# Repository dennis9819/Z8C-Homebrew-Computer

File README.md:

# Z8C-Homebrew-Computer

# Using the build tools
The Z8C uses the zmac macro assembler (http://48k.ca/zmac.html)

To easily develop for my Z80 homebrew system, I designed a simple
assempler development environment. This packs the following tasks into one script:
* zmac assembly
* object file creation (for xmodem upload)
* monitor file creation (creates monitor commands for ascii upload)
* symbol table include file generation
* eeprom programming for the minipro

## Prequisites
* zmac - self-compiled version included in ./Utility.
* minipro (https://gitlab.com/DavidGriffith/minipro)
* binutils (apt-get install binutils-multiarch, 
    pacman -S aarch64-linux-gnu-binutils )

## Building a project
`./build.sh <dir> <asm filename>`
* `dir`: Path to the location of the asm file
* `asm filename`: name of the assembly file without suffix

```
    # e.g.:
    cd ./Utility
    ./build.sh ../OperatingSystem/monitor_v2  
    ./build.sh ../OperatingSystem/software  
```
## Building a project with a properties file

`./build.sh <dir>`
* `dir`: Path to the location of the asm file

The directory must contain a file called `properties.env`
This file can contain project-specific options.

Example:
```
export OPT_GEN_SYMBOLTABLE=1
export OPT_GEN_MONFILE=0
export OPT_GEN_OBJFILE=1
export OPT_WRITEROM=1
export FILENAME=main
```

### Options
* `OPT_GEN_SYMBOLTABLE` if set to 1: Generates the symbols.s file
* `OPT_GEN_MONFILE` if set to 1: Generates the monitor file
* `OPT_GEN_OBJFILE` if set to 1: Generates the object file
* `OPT_WRITEROM` if set to 1: Starts eeprom programmer
* `FILENAME` same as the `<asm filename>` paramter of the build script
* `ROOT_DIR` overrides the project root path. required if git is not used
* `EEPROM_PART` sets EEPROM part for minipro. Default: `AT28C256`

# System design
The Z80 Hombrew computer is modular computer system, designed arround a custom backplane.

## Available modules
### Z8C CPU/COM Board
* Z80 ZPU @ 4MHz (6MHz planned)
* 64 KiB SRAM
* 32 KiB EEPROM (R/W switchable)
* Z80 CTC with external 1.8432MHz Clock switchable per channel
* Z80 SIO (Up to 115200 BAUD possible @ X16 SIO prescaler)
* 1 FTDI Connector
* 1 RS232 DSUB-9 Port
* 8 front-facing DIP switches (currently used for baud-rate setup)
* Power-On-Reset Circuit

```
Memory Layout
       Default ($00 = 0x00)  Mode 1 ($00 = 0x02)  Mode 2 ($00 = 0x01)             
$0000 +--------------------+--------------------+--------------------+
      | EEPROM Lower 16KiB | EEPROM Upper 16KiB | SRAM               |
$4000 +--------------------+--------------------+                    |
      | SRAM               | SRAM               |                    | 
      |                    |                    |                    |
      |                    |                    |                    |
$FFFF +--------------------+--------------------+--------------------+

Note: In default mode and mode 1, the MEMAQ pin (pin a5 on backplane) 
      can be used to inject an external memory device in the $0000-$3FFF 
      window.

IO Addresses:
$00 Memory register
$01 DIP Switches
$04 CTC (First address)
$08 SIO (First address)
```

### Z8C MIO Board
* Z80 PIO (Used for GPIO and non Z80 compliant interrupt handling)
* VT82C42 PS/2 controller
* AM5911A (only usable with CPU-Clock under 3 MHz)
* PFC8584 I2C Controller
* DS1307 RTC
* 8-Bit GPIO Port

//TODO: Add more Info

### Z8C Disk Interface Board
* Intel 82C55 based IDE Interface
* FDC9266 Floppy Disk Controller

//TODO: Add more Info

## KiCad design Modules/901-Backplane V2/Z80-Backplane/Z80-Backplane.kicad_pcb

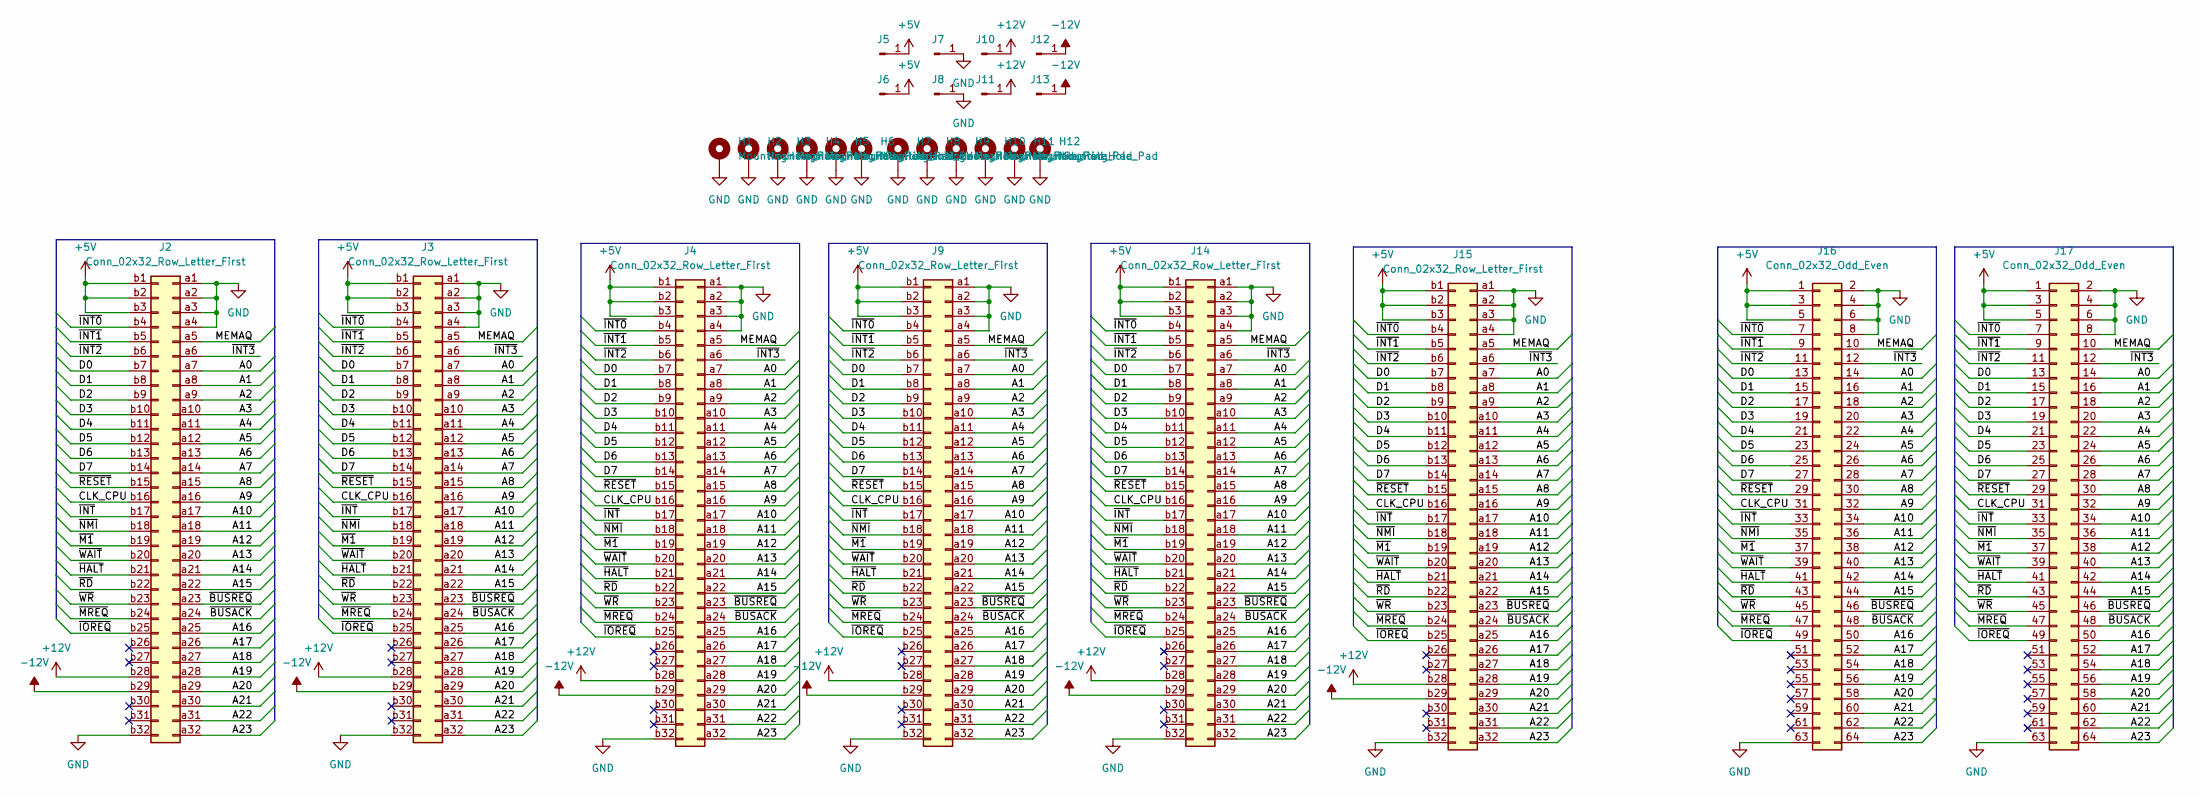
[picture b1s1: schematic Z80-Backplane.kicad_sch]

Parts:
H1, H2, H3, H4, H5, H6, H7, H8, H9, H10, H11, H12: MountingHole_Pad; MountingHole_2.7mm_M2.5_DIN965_Pad
J2, J3, J4, J9, J14, J15: Conn_02x32_Row_Letter_First; DIN41612_B_2x32_Female_Vertical_THT
J5, J6, J7, J8, J10, J11, J12, J13: Conn_01x01_Male; FS-P475
J16, J17: Conn_02x32_Odd_Even; IDC-Header_2x32_P2.54mm_Vertical

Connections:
+5V: J2.b1, J2.b2, J2.b3, J3.b1, J3.b2, J3.b3, J4.b1, J4.b2, J4.b3, J5.1, J6.1, J9.b1, J9.b2, J9.b3, J14.b1, J14.b2, J14.b3, J15.b1, J15.b2, J15.b3, J16.1, J16.3, J16.5, J17.1, J17.3, J17.5
+12V: J2.b28, J3.b28, J4.b28, J9.b28, J10.1, J11.1, J14.b28, J15.b28
-12V: J2.b29, J3.b29, J4.b29, J9.b29, J12.1, J13.1, J14.b29, J15.b29
/A0: J2.a7, J3.a7, J4.a7, J9.a7, J14.a7, J15.a7, J16.14, J17.14
/A1: J2.a8, J3.a8, J4.a8, J9.a8, J14.a8, J15.a8, J16.16, J17.16
/A2: J2.a9, J3.a9, J4.a9, J9.a9, J14.a9, J15.a9, J16.18, J17.18
/A3: J2.a10, J3.a10, J4.a10, J9.a10, J14.a10, J15.a10, J16.20, J17.20
/A4: J2.a11, J3.a11, J4.a11, J9.a11, J14.a11, J15.a11, J16.22, J17.22
/A5: J2.a12, J3.a12, J4.a12, J9.a12, J14.a12, J15.a12, J16.24, J17.24
/A6: J2.a13, J3.a13, J4.a13, J9.a13, J14.a13, J15.a13, J16.26, J17.26
/A7: J2.a14, J3.a14, J4.a14, J9.a14, J14.a14, J15.a14, J16.28, J17.28
/A8: J2.a15, J3.a15, J4.a15, J9.a15, J14.a15, J15.a15, J16.30, J17.30
/A9: J2.a16, J3.a16, J4.a16, J9.a16, J14.a16, J15.a16, J16.32, J17.32
/A10: J2.a17, J3.a17, J4.a17, J9.a17, J14.a17, J15.a17, J16.34, J17.34
/A11: J2.a18, J3.a18, J4.a18, J9.a18, J14.a18, J15.a18, J16.36, J17.36
/A12: J2.a19, J3.a19, J4.a19, J9.a19, J14.a19, J15.a19, J16.38, J17.38
/A13: J2.a20, J3.a20, J4.a20, J9.a20, J14.a20, J15.a20, J16.40, J17.40
/A14: J2.a21, J3.a21, J4.a21, J9.a21, J14.a21, J15.a21, J16.42, J17.42
/A15: J2.a22, J3.a22, J4.a22, J9.a22, J14.a22, J15.a22, J16.44, J17.44
/A16: J2.a25, J3.a25, J4.a25, J9.a25, J14.a25, J15.a25, J16.50, J17.50
/A17: J2.a26, J3.a26, J4.a26, J9.a26, J14.a26, J15.a26, J16.52, J17.52
/A18: J2.a27, J3.a27, J4.a27, J9.a27, J14.a27, J15.a27, J16.54, J17.54
/A19: J2.a28, J3.a28, J4.a28, J9.a28, J14.a28, J15.a28, J16.56, J17.56
/A20: J2.a29, J3.a29, J4.a29, J9.a29, J14.a29, J15.a29, J16.58, J17.58
/A21: J2.a30, J3.a30, J4.a30, J9.a30, J14.a30, J15.a30, J16.60, J17.60
/A22: J2.a31, J3.a31, J4.a31, J9.a31, J14.a31, J15.a31, J16.62, J17.62
/A23: J2.a32, J3.a32, J4.a32, J9.a32, J14.a32, J15.a32, J16.64, J17.64
/CLK_CPU: J2.b16, J3.b16, J4.b16, J9.b16, J14.b16, J15.b16, J16.31, J17.31
/D0: J2.b7, J3.b7, J4.b7, J9.b7, J14.b7, J15.b7, J16.13, J17.13
/D1: J2.b8, J3.b8, J4.b8, J9.b8, J14.b8, J15.b8, J16.15, J17.15
/D2: J2.b9, J3.b9, J4.b9, J9.b9, J14.b9, J15.b9, J16.17, J17.17
/D3: J2.b10, J3.b10, J4.b10, J9.b10, J14.b10, J15.b10, J16.19, J17.19
/D4: J2.b11, J3.b11, J4.b11, J9.b11, J14.b11, J15.b11, J16.21, J17.21
/D5: J2.b12, J3.b12, J4.b12, J9.b12, J14.b12, J15.b12, J16.23, J17.23
/D6: J2.b13, J3.b13, J4.b13, J9.b13, J14.b13, J15.b13, J16.25, J17.25
/D7: J2.b14, J3.b14, J4.b14, J9.b14, J14.b14, J15.b14, J16.27, J17.27
/MEMAQ: J2.a5, J3.a5, J4.a5, J9.a5, J14.a5, J15.a5, J16.10, J17.10
/~BUSACK: J2.a24, J3.a24, J4.a24, J9.a24, J14.a24, J15.a24, J16.48, J17.48
/~BUSREQ: J2.a23, J3.a23, J4.a23, J9.a23, J14.a23, J15.a23, J16.46, J17.46
/~HALT: J2.b21, J3.b21, J4.b21, J9.b21, J14.b21, J15.b21, J16.41, J17.41
/~INT0: J2.b4, J3.b4, J4.b4, J9.b4, J14.b4, J15.b4, J16.7, J17.7
/~INT1: J2.b5, J3.b5, J4.b5, J9.b5, J14.b5, J15.b5, J16.9, J17.9
/~INT2: J2.b6, J3.b6, J4.b6, J9.b6, J14.b6, J15.b6, J16.11, J17.11
/~INT3: J2.a6, J3.a6, J4.a6, J9.a6, J14.a6, J15.a6, J16.12, J17.12
/~INT: J2.b17, J3.b17, J4.b17, J9.b17, J14.b17, J15.b17, J16.33, J17.33
/~IOREQ: J2.b25, J3.b25, J4.b25, J9.b25, J14.b25, J15.b25, J16.49, J17.49
/~M1: J2.b19, J3.b19, J4.b19, J9.b19, J14.b19, J15.b19, J16.37, J17.37
/~MREQ: J2.b24, J3.b24, J4.b24, J9.b24, J14.b24, J15.b24, J16.47, J17.47
/~NMI: J2.b18, J3.b18, J4.b18, J9.b18, J14.b18, J15.b18, J16.35, J17.35
/~RD: J2.b22, J3.b22, J4.b22, J9.b22, J14.b22, J15.b22, J16.43, J17.43
/~RESET: J2.b15, J3.b15, J4.b15, J9.b15, J14.b15, J15.b15, J16.29, J17.29
/~WAIT: J2.b20, J3.b20, J4.b20, J9.b20, J14.b20, J15.b20, J16.39, J17.39
/~WR: J2.b23, J3.b23, J4.b23, J9.b23, J14.b23, J15.b23, J16.45, J17.45
GND: H1.1, H2.1, H3.1, H4.1, H5.1, H6.1, H7.1, H8.1, H9.1, H10.1, H11.1, H12.1, J2.a1, J2.a2, J2.a3, J2.a4, J2.b32, J3.a1, J3.a2, J3.a3, J3.a4, J3.b32, J4.a1, J4.a2, J4.a3, J4.a4, J4.b32, J7.1, J8.1, J9.a1, J9.a2, J9.a3, J9.a4, J9.b32, J14.a1, J14.a2, J14.a3, J14.a4, J14.b32, J15.a1, J15.a2, J15.a3, J15.a4, J15.b32, J16.2, J16.4, J16.6, J16.8, J16.63, J17.2, J17.4, J17.6, J17.8, J17.63

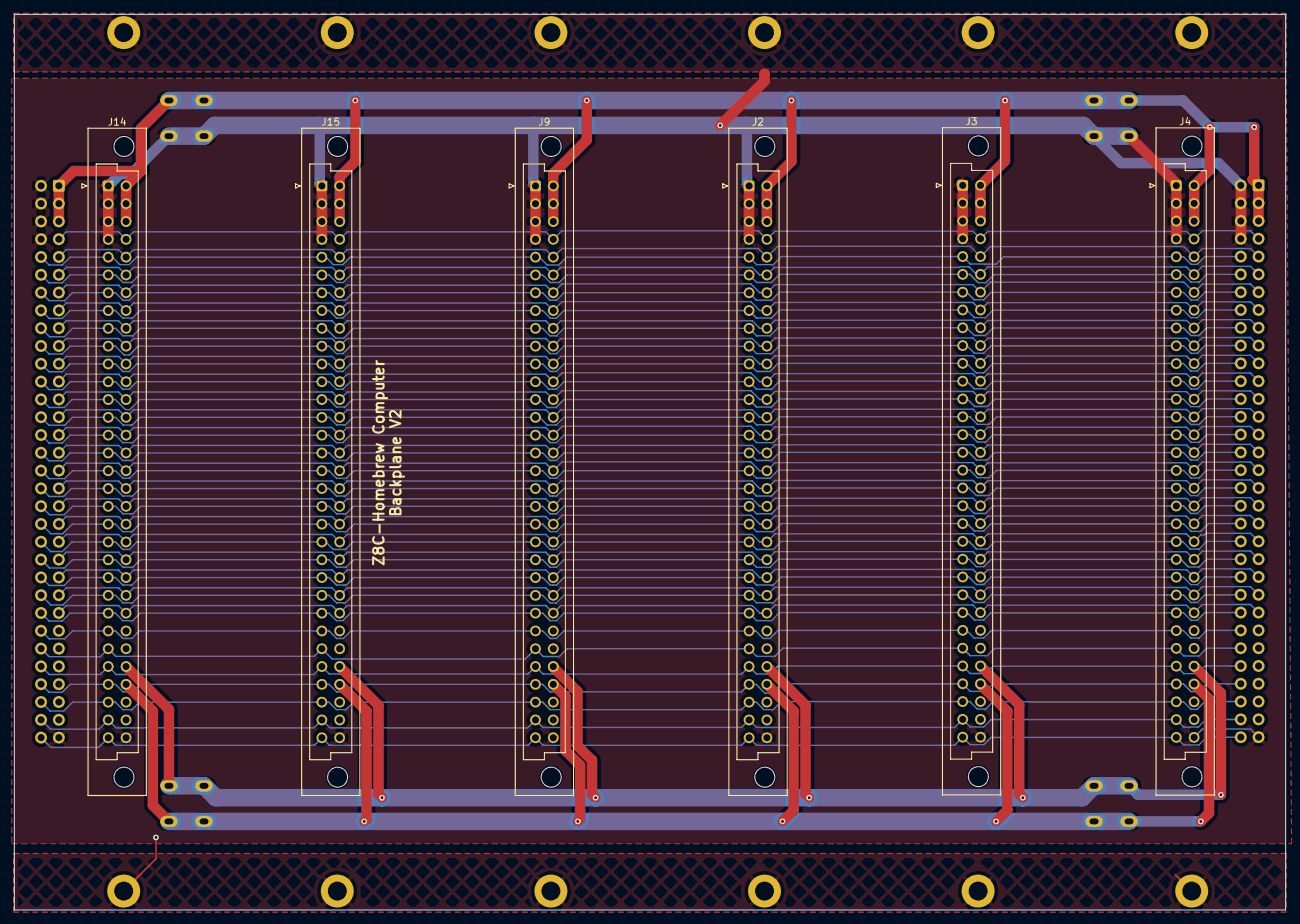
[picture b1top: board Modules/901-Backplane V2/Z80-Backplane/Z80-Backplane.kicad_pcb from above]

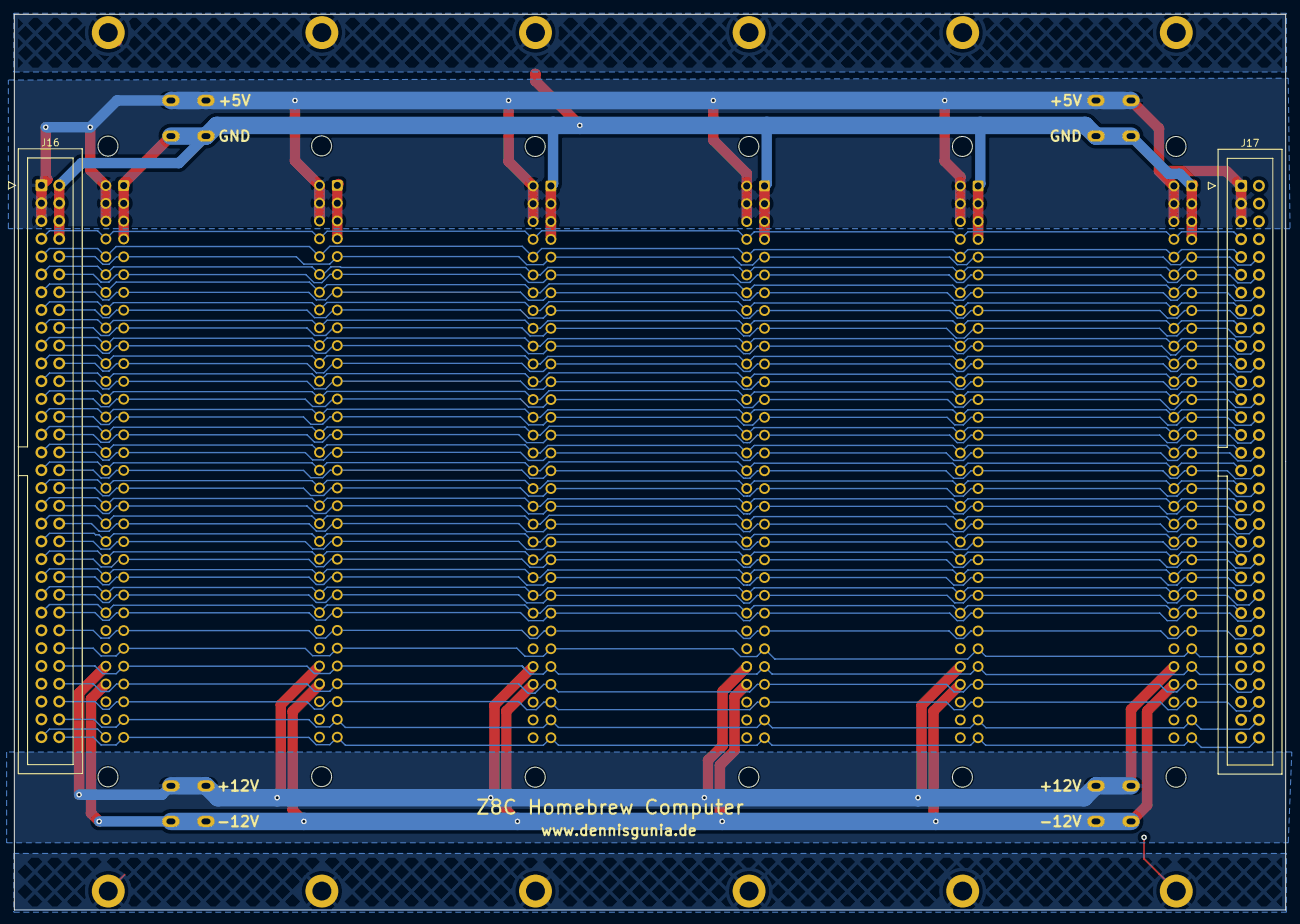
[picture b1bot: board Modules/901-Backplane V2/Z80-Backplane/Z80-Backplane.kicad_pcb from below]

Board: 2 copper layers, 181.4 x 127.8 mm, 28 parts (10 on the bottom side), 54 nets.

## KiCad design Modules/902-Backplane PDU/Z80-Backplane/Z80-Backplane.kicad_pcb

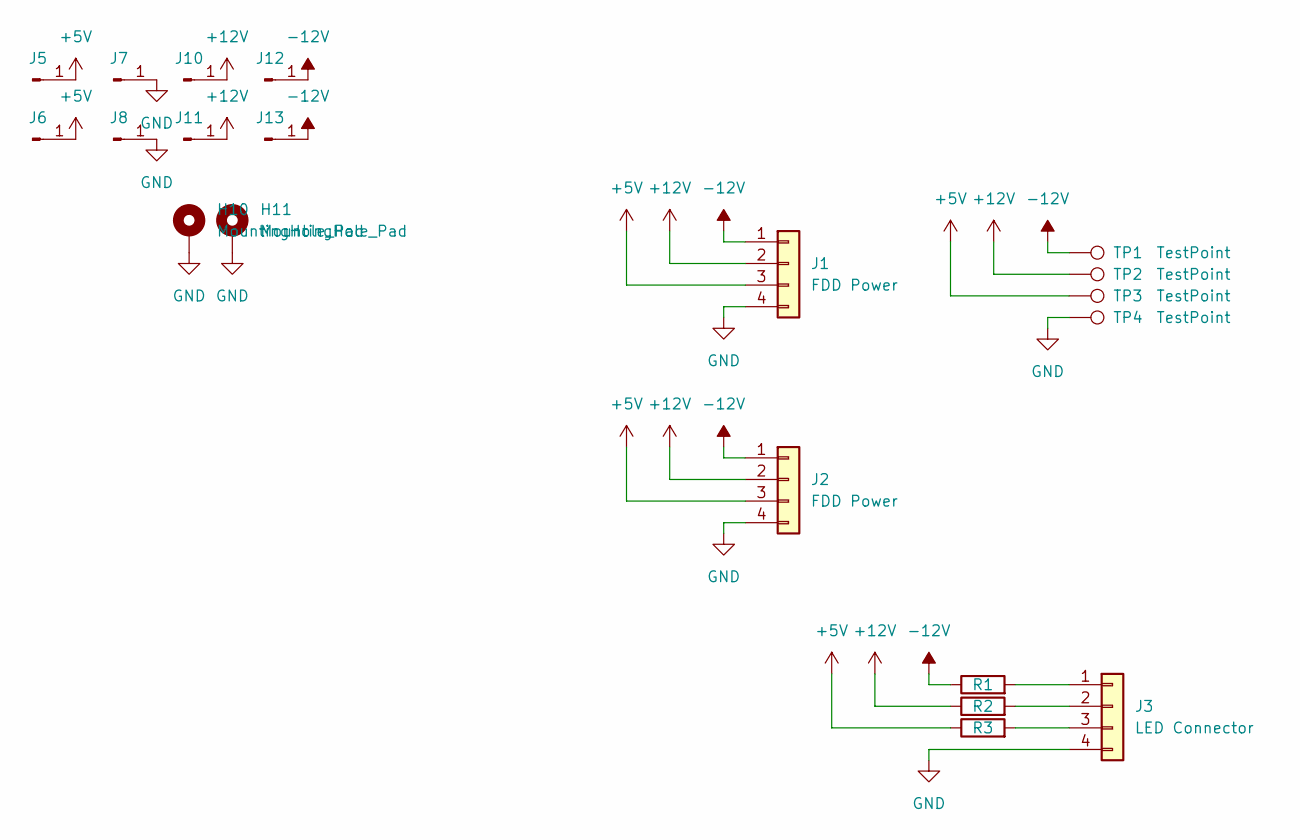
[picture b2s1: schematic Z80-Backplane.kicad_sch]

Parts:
H10, H11: MountingHole_Pad; MountingHole_2.7mm_M2.5_DIN965_Pad
J1, J2: FDD Power; Molex_Mini-Fit_Jr_5566-04A_2x02_P4.20mm_Vertical
J3: LED Connector; JST_EH_B4B-EH-A_1x04_P2.50mm_Vertical
J5, J6, J7, J8, J10, J11, J12, J13: Conn_01x01_Male; FS-P475
R1, R2, R3: R; R_Axial_DIN0207_L6.3mm_D2.5mm_P10.16mm_Horizontal
TP1, TP2, TP3, TP4: TestPoint; TestPoint_THTPad_D1.5mm_Drill0.7mm

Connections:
+5V: J1.3, J2.3, J5.1, J6.1, R3.1, TP3.1
+12V: J1.2, J2.2, J10.1, J11.1, R2.1, TP2.1
-12V: J1.1, J2.1, J12.1, J13.1, R1.1, TP1.1
GND: H10.1, H11.1, J1.4, J2.4, J3.4, J7.1, J8.1, TP4.1
unnamed: J3.1, R1.2
unnamed: J3.2, R2.2
unnamed: J3.3, R3.2

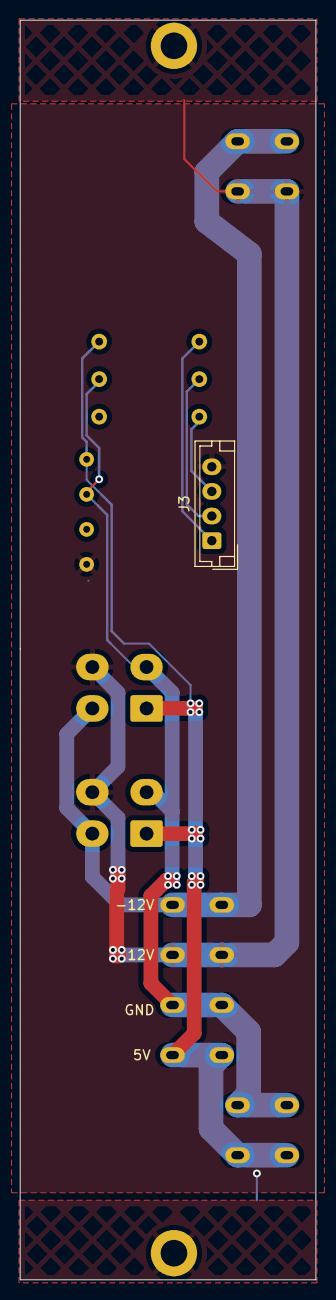
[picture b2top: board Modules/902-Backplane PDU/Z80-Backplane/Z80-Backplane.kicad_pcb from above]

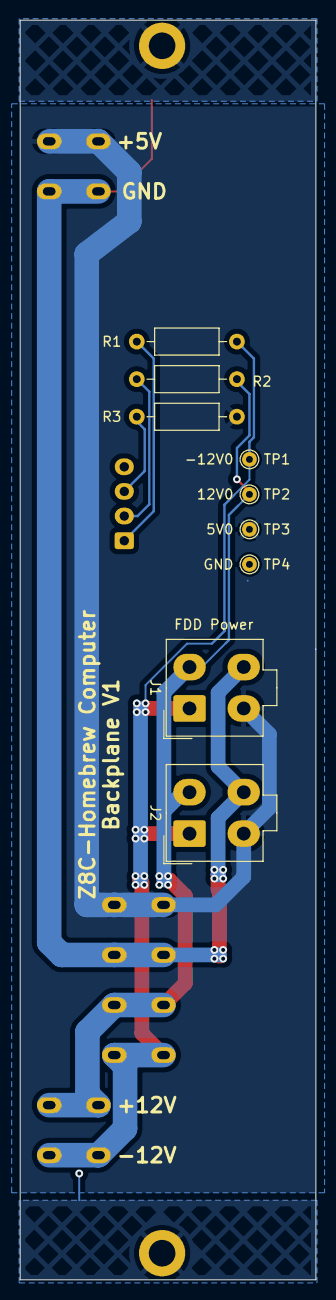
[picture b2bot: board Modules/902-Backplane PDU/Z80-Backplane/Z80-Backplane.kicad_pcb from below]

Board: 2 copper layers, 30.0 x 127.8 mm, 20 parts (13 on the bottom side), 7 nets.

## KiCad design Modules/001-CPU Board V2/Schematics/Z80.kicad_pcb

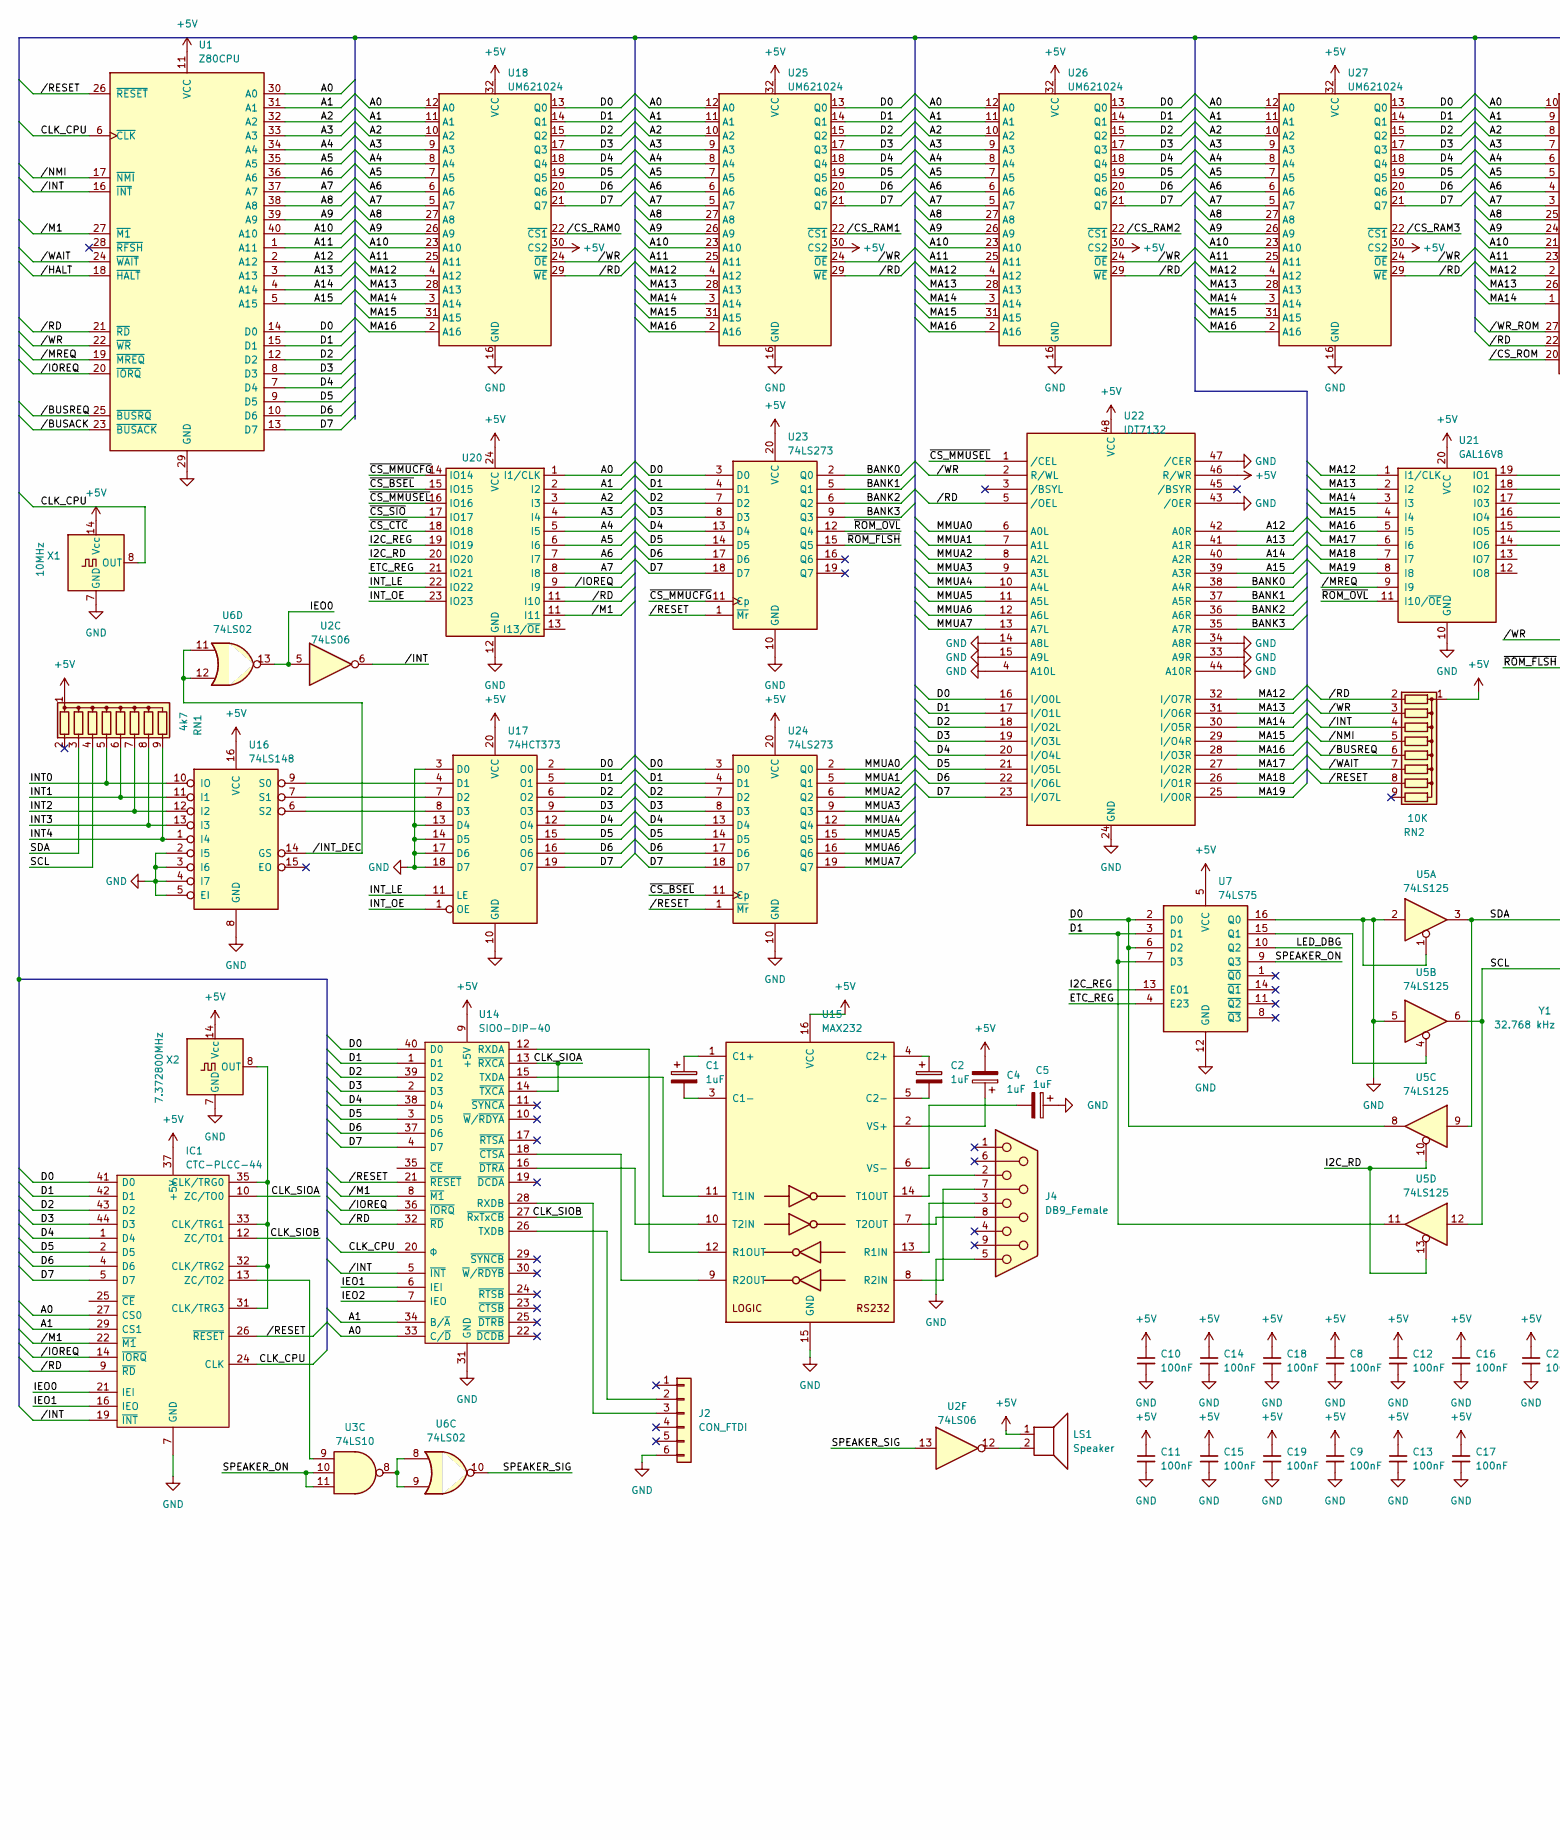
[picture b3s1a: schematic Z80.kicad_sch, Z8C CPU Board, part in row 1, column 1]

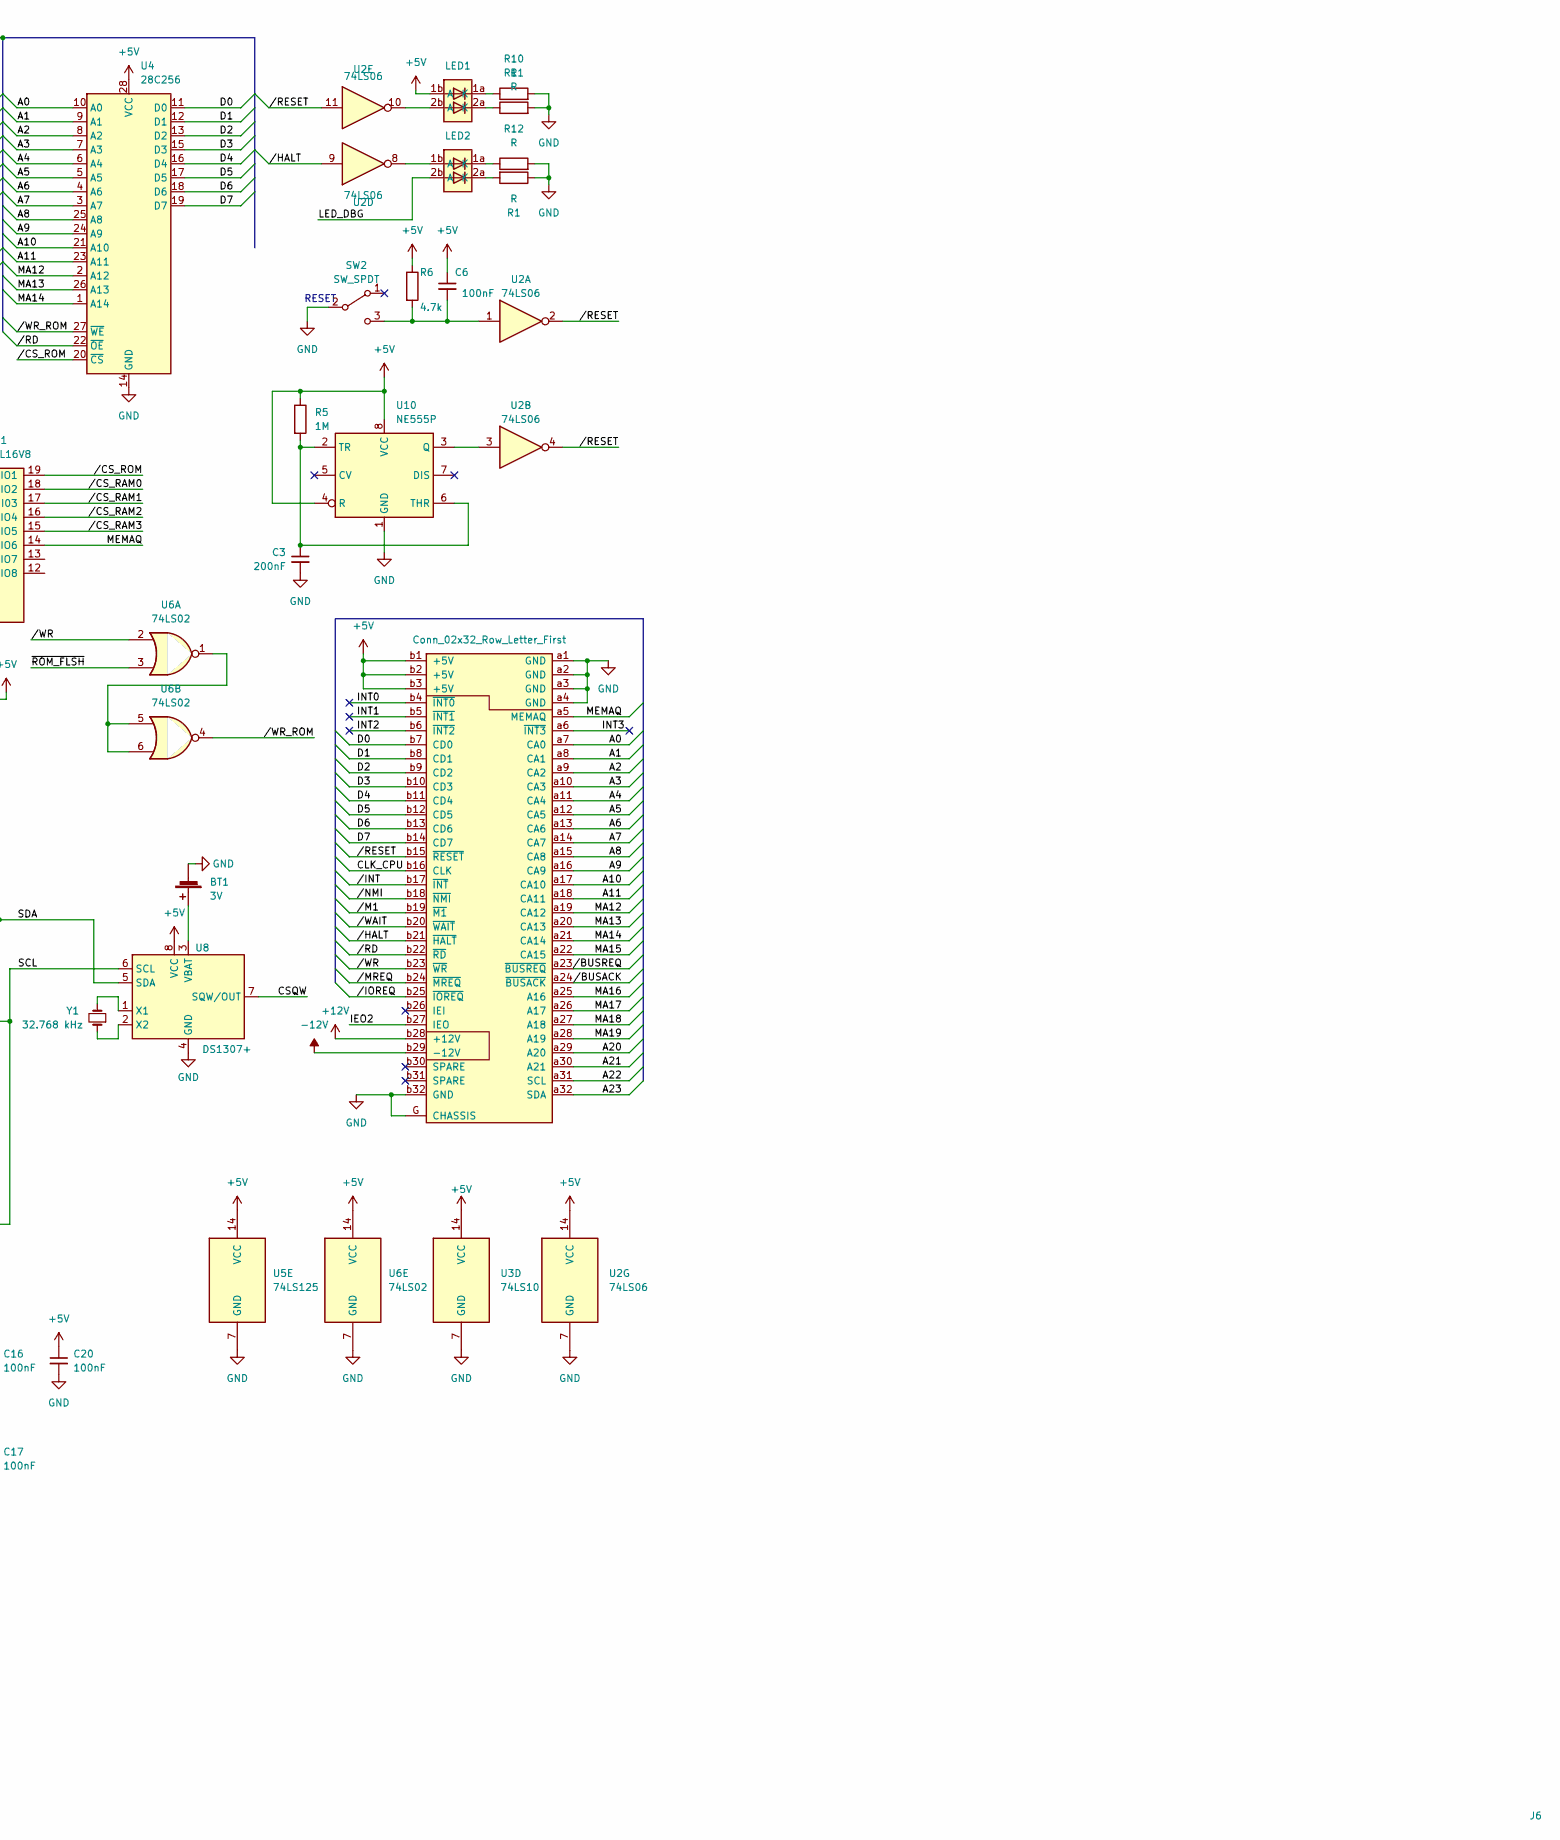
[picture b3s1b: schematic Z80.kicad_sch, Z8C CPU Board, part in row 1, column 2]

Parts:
BT1: 3V; Battery_Holder_Coin_2032_BS-7
C1, C2, C4, C5: 1uF; CP_Radial_D6.3mm_P2.50mm
C3: 200nF; C_Rect_L7.0mm_W2.0mm_P5.00mm
C6, C8, C9, C10, C11, C12, C13, C14, C15, C16, C17, C18, C19, C20: 100nF; C_Rect_L7.0mm_W2.0mm_P5.00mm
IC1: CTC-PLCC-44; PLCC-44_THT-Socket; Manufacturer_Part_Number Z84C3010PEG; Mouser Part Number 692-Z84C3010PEG
J2: CON_FTDI; PinSocket_1x06_P2.54mm_Vertical
J4: DB9_Female; DSUB-9_Female_Horizontal_P2.77x2.84mm_EdgePinOffset9.90mm_H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
J6: Conn_02x32_Row_Letter_First; Z8C Card
LED1, LED2: MENOTR_A500_Dual_3mm; MENTOR A500 Dual 3mm
LS1: Speaker; Piezo_Transducer_THT_PS1240P02BT
R1, R10, R11, R12: R; R_Axial_DIN0204_L3.6mm_D1.6mm_P2.54mm_Vertical
R5: 1M; R_Axial_DIN0204_L3.6mm_D1.6mm_P2.54mm_Vertical
R6: 4.7k; R_Axial_DIN0204_L3.6mm_D1.6mm_P2.54mm_Vertical
RN1: 4k7; R_Array_SIP9
RN2: 10K; R_Array_SIP9
SW2: SW_SPDT; Toggle_Switch_100SP1T2B4M6QE
U1: Z80CPU; DIP-40_W15.24mm_Socket_LongPads
U2: 74LS06; DIP-14_W7.62mm
U3: 74LS10
U4: 28C256; DIP_Socket-28_W11.9_W12.7_W15.24_W17.78_W18.5_3M_228-1277-0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
U5: 74LS125; DIP-14_W7.62mm_Socket
U6: 74LS02
U7: 74LS75; DIP-16_W7.62mm_Socket
U8: DS1307+; DIP-8_W7.62mm
U10: NE555P; DIP-8_W7.62mm_Socket_LongPads
U14: SIO0-DIP-40; DIP-40_W15.24mm_Socket_LongPads; Manufacturer_Part_Number Z84C4206PEG; Mouser Part Number 692-Z84C4206PEG
U15: MAX232; DIP-16_W7.62mm_Socket_LongPads
U16: 74LS148; DIP-16_W7.62mm
U17: 74HCT373; DIP-20_W7.62mm
U18, U25, U26, U27: UM621024; DIP-32_W7.62mm
U20: DIP-24_W7.62mm
U21: GAL16V8; DIP-20_W7.62mm_Socket_LongPads
U22: IDT7132; PLCC-52_THT-Socket
U23, U24: 74LS273; DIP-20_W7.62mm
X1: 10MHz; Oscillator_DIP-14
X2: 7.372800MHz; Oscillator_DIP-14
Y1: 32.768 kHz; Crystal_AT310_D3.0mm_L10.0mm_Horizontal

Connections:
+5V: C4.2, C6.1, C8.1, C9.1, C10.1, C11.1, C12.1, C13.1, C14.1, C15.1, C16.1, C17.1, C18.1, C19.1, C20.1, IC1.37 (+5V), J6.b1 (+5V), J6.b2 (+5V), J6.b3 (+5V), LED1.1b (A), LS1.1, R5.1, R6.1, RN1.1 (common), RN2.1 (common), U1.11 (VCC), U2.14 (VCC), U3.14 (VCC), U4.28 (VCC), U5.14 (VCC), U6.14 (VCC), U7.5 (VCC), U8.8 (VCC), U10.4 (R), U10.8 (VCC), U14.9 (+5V), U15.16 (VCC), U16.16 (VCC), U17.20 (VCC), U18.30 (CS2), U18.32 (VCC), U20.24 (VCC), U21.20 (VCC), U22.46 (R/WR), U22.48 (VCC), U23.20 (VCC), U24.20 (VCC), U25.30 (CS2), U25.32 (VCC), U26.30 (CS2), U26.32 (VCC), U27.30 (CS2), U27.32 (VCC), X1.14 (Vcc), X2.14 (Vcc)
+12V: J6.b28 (+12V)
-12V: J6.b29 (-12V)
/A0: IC1.27 (CS0), J6.a7 (CA0), U1.30 (A0), U4.10 (A0), U14.33 (C/~D), U18.12 (A0), U20.1 (I1/CLK), U25.12 (A0), U26.12 (A0), U27.12 (A0)
/A1: IC1.29 (CS1), J6.a8 (CA1), U1.31 (A1), U4.9 (A1), U14.34 (B/~A), U18.11 (A1), U20.2 (I2), U25.11 (A1), U26.11 (A1), U27.11 (A1)
/A2: J6.a9 (CA2), U1.32 (A2), U4.8 (A2), U18.10 (A2), U20.3 (I3), U25.10 (A2), U26.10 (A2), U27.10 (A2)
/A3: J6.a10 (CA3), U1.33 (A3), U4.7 (A3), U18.9 (A3), U20.4 (I4), U25.9 (A3), U26.9 (A3), U27.9 (A3)
/A4: J6.a11 (CA4), U1.34 (A4), U4.6 (A4), U18.8 (A4), U20.5 (I5), U25.8 (A4), U26.8 (A4), U27.8 (A4)
/A5: J6.a12 (CA5), U1.35 (A5), U4.5 (A5), U18.7 (A5), U20.6 (I6), U25.7 (A5), U26.7 (A5), U27.7 (A5)
/A6: J6.a13 (CA6), U1.36 (A6), U4.4 (A6), U18.6 (A6), U20.7 (I7), U25.6 (A6), U26.6 (A6), U27.6 (A6)
/A7: J6.a14 (CA7), U1.37 (A7), U4.3 (A7), U18.5 (A7), U20.8 (I8), U25.5 (A7), U26.5 (A7), U27.5 (A7)
/A8: J6.a15 (CA8), U1.38 (A8), U4.25 (A8), U18.27 (A8), U25.27 (A8), U26.27 (A8), U27.27 (A8)
/A9: J6.a16 (CA9), U1.39 (A9), U4.24 (A9), U18.26 (A9), U25.26 (A9), U26.26 (A9), U27.26 (A9)
/A10: J6.a17 (CA10), U1.40 (A10), U4.21 (A10), U18.23 (A10), U25.23 (A10), U26.23 (A10), U27.23 (A10)
/A11: J6.a18 (CA11), U1.1 (A11), U4.23 (A11), U18.25 (A11), U25.25 (A11), U26.25 (A11), U27.25 (A11)
/A12: U1.2 (A12), U22.42 (A0R)
/A13: U1.3 (A13), U22.41 (A1R)
/A14: U1.4 (A14), U22.40 (A2R)
/A15: U1.5 (A15), U22.39 (A3R)
/A20: J6.a29 (A20)
/A21: J6.a30 (A21)
/A22: J6.a31 (SCL)
/A23: J6.a32 (SDA)
/BANK0: U22.38 (A4R), U23.2 (Q0)
/BANK1: U22.37 (A5R), U23.5 (Q1)
/BANK2: U22.36 (A6R), U23.6 (Q2)
/BANK3: U22.35 (A7R), U23.9 (Q3)
/CLK_CPU: IC1.24 (CLK), J6.b16 (CLK), U1.6 (~CLK), U14.20 (Φ), X1.8 (OUT)
/CLK_SIOA: IC1.10 (ZC/TO0), U14.13 (~RXCA), U14.14 (~TXCA)
/CLK_SIOB: IC1.12 (ZC/TO1), U14.27 (~RxTxCB)
/CSQW: U8.7 (SQW/OUT)
/D0: IC1.41 (D0), J6.b7 (CD0), U1.14 (D0), U4.11 (D0), U5.8, U7.2 (D0), U7.6 (D2), U14.40 (D0), U17.2 (O0), U18.13 (Q0), U22.16 (I/O0L), U23.3 (D0), U24.3 (D0), U25.13 (Q0), U26.13 (Q0), U27.13 (Q0)
/D1: IC1.42 (D1), J6.b8 (CD1), U1.15 (D1), U4.12 (D1), U5.11, U7.3 (D1), U7.7 (D3), U14.1 (D1), U17.5 (O1), U18.14 (Q1), U22.17 (I/O1L), U23.4 (D1), U24.4 (D1), U25.14 (Q1), U26.14 (Q1), U27.14 (Q1)
/D2: IC1.43 (D2), J6.b9 (CD2), U1.12 (D2), U4.13 (D2), U14.39 (D2), U17.6 (O2), U18.15 (Q2), U22.18 (I/O2L), U23.7 (D2), U24.7 (D2), U25.15 (Q2), U26.15 (Q2), U27.15 (Q2)
/D3: IC1.44 (D3), J6.b10 (CD3), U1.8 (D3), U4.15 (D3), U14.2 (D3), U17.9 (O3), U18.17 (Q3), U22.19 (I/O3L), U23.8 (D3), U24.8 (D3), U25.17 (Q3), U26.17 (Q3), U27.17 (Q3)
/D4: IC1.1 (D4), J6.b11 (CD4), U1.7 (D4), U4.16 (D4), U14.38 (D4), U17.12 (O4), U18.18 (Q4), U22.20 (I/O4L), U23.13 (D4), U24.13 (D4), U25.18 (Q4), U26.18 (Q4), U27.18 (Q4)
/D5: IC1.2 (D5), J6.b12 (CD5), U1.9 (D5), U4.17 (D5), U14.3 (D5), U17.15 (O5), U18.19 (Q5), U22.21 (I/O5L), U23.14 (D5), U24.14 (D5), U25.19 (Q5), U26.19 (Q5), U27.19 (Q5)
/D6: IC1.4 (D6), J6.b13 (CD6), U1.10 (D6), U4.18 (D6), U14.37 (D6), U17.16 (O6), U18.20 (Q6), U22.22 (I/O6L), U23.17 (D6), U24.17 (D6), U25.20 (Q6), U26.20 (Q6), U27.20 (Q6)
/D7: IC1.5 (D7), J6.b14 (CD7), U1.13 (D7), U4.19 (D7), U14.4 (D7), U17.19 (O7), U18.21 (Q7), U22.23 (I/O7L), U23.18 (D7), U24.18 (D7), U25.21 (Q7), U26.21 (Q7), U27.21 (Q7)
/ETC_REG: U7.4 (E23), U20.21 (IO21)
/I2C_RD: U5.10, U5.13, U20.20 (IO20)
/I2C_REG: U7.13 (E01), U20.19 (IO19)
/IEO0: IC1.21 (IEI), U2.5, U6.13
/IEO1: IC1.16 (IEO), U14.6 (IEI)
/IEO2: J6.b27 (IEO), U14.7 (IEO)
/INT0: J6.b4 (~INT0), RN1.5 (R4), U16.10 (IO)
/INT1: J6.b5 (~INT1), RN1.6 (R5), U16.11 (I1)
/INT2: J6.b6 (~INT2), RN1.7 (R6), U16.12 (I2)
/INT3: J6.a6 (~INT3), RN1.8 (R7), U16.13 (I3)
/INT4: RN1.9 (R8), U16.1 (I4)
/INT_LE: U17.11 (LE), U20.22 (IO22)
/INT_OE: U17.1 (OE), U20.23 (IO23)
/LED_DBG: LED2.2b (A), U7.10 (Q2)
/MA12: J6.a19 (CA12), U4.2 (A12), U18.4 (A12), U21.1 (I1/CLK), U22.32 (I/O7R), U25.4 (A12), U26.4 (A12), U27.4 (A12)
/MA13: J6.a20 (CA13), U4.26 (A13), U18.28 (A13), U21.2 (I2), U22.31 (I/O6R), U25.28 (A13), U26.28 (A13), U27.28 (A13)
/MA14: J6.a21 (CA14), U4.1 (A14), U18.3 (A14), U21.3 (I3), U22.30 (I/O5R), U25.3 (A14), U26.3 (A14), U27.3 (A14)
/MA15: J6.a22 (CA15), U18.31 (A15), U21.4 (I4), U22.29 (I/O4R), U25.31 (A15), U26.31 (A15), U27.31 (A15)
/MA16: J6.a25 (A16), U18.2 (A16), U21.5 (I5), U22.28 (I/O3R), U25.2 (A16), U26.2 (A16), U27.2 (A16)
/MA17: J6.a26 (A17), U21.6 (I6), U22.27 (I/O2R)
/MA18: J6.a27 (A18), U21.7 (I7), U22.26 (I/O1R)
/MA19: J6.a28 (A19), U21.8 (I8), U22.25 (I/O0R)
/MEMAQ: J6.a5 (MEMAQ), U21.14 (IO6)
/MMUA0: U22.6 (A0L), U24.2 (Q0)
/MMUA1: U22.7 (A1L), U24.5 (Q1)
/MMUA2: U22.8 (A2L), U24.6 (Q2)
/MMUA3: U22.9 (A3L), U24.9 (Q3)
/MMUA4: U22.10 (A4L), U24.12 (Q4)
/MMUA5: U22.11 (A5L), U24.15 (Q5)
/MMUA6: U22.12 (A6L), U24.16 (Q6)
/MMUA7: U22.13 (A7L), U24.19 (Q7)
/SCL: RN1.4 (R3), U5.6, U5.12, U8.6 (SCL)
/SDA: RN1.3 (R2), U5.3, U5.9, U8.5 (SDA)
/SPEAKER_ON: U3.10, U3.11, U7.9 (Q3)
/SPEAKER_SIG: U2.13, U6.10
//BUSACK: J6.a24 (~BUSACK), U1.23 (~BUSACK)
//BUSREQ: J6.a23 (~BUSREQ), RN2.6 (R5), U1.25 (~BUSRQ)
//CS_RAM0: U18.22 (~CS1), U21.18 (IO2)
//CS_RAM1: U21.17 (I03), U25.22 (~CS1)
//CS_RAM2: U21.16 (IO4), U26.22 (~CS1)
//CS_RAM3: U21.15 (IO5), U27.22 (~CS1)
//CS_ROM: U4.20 (~CS), U21.19 (IO1)
//HALT: J6.b21 (~HALT), U1.18 (~HALT), U2.9
//INT: IC1.19 (~INT), J6.b17 (~INT), RN2.4 (R3), U1.16 (~INT), U2.6, U14.5 (~INT)
//INT_DEC: U6.11, U6.12, U16.14 (GS)
//IOREQ: IC1.14 (~IORQ), J6.b25 (~IOREQ), U1.20 (~IORQ), U14.36 (~IORQ), U20.9 (I9)
//MREQ: J6.b24 (~MREQ), U1.19 (~MREQ), U21.9 (I9)
//NMI: J6.b18 (~NMI), RN2.5 (R4), U1.17 (~NMI)
//RESET: IC1.26 (~RESET), J6.b15 (~RESET), RN2.8 (R7), U1.26 (~RESET), U2.2, U2.4, U2.11, U14.21 (~RESET), U23.1 (~Mr), U24.1 (~Mr)
//WAIT: J6.b20 (~WAIT), RN2.7 (R6), U1.24 (~WAIT)
//WR_ROM: U4.27 (~WE), U6.4
/~CS_BSEL: U20.15 (IO15), U24.11 (Cp)
/~CS_CTC: U20.18 (IO18)
/~CS_MMUCFG: U20.14 (IO14), U23.11 (Cp)
/~CS_MMUSEL: U20.16 (IO16), U22.1 (/CEL)
/~CS_SIO: U20.17 (IO17)
/~ROM_FLSH: U6.3, U23.15 (Q5)
/~ROM_OVL: U21.11 (I10/~OE), U23.12 (Q4)
unnamed: IC1.31 (CLK/TRG3), IC1.32 (CLK/TRG2), IC1.33 (CLK/TRG1), IC1.35 (CLK/TRG0), X2.8 (OUT)
unnamed: IC1.13 (ZC/TO2), U3.9
unnamed: J2.2, U14.26 (TXDB)
unnamed: J2.3, U14.28 (RXDB)
unnamed: LED1.2b (A), U2.10
unnamed: LED1.1a (K), R10.1
unnamed: LED1.2a (K), R11.1
unnamed: LED2.1b (A), U2.8
unnamed: LED2.1a (K), R12.1
unnamed: LED2.2a (K), R1.2
unnamed: LS1.2, U2.12
unnamed: C6.2, R6.2, SW2.3 (C), U2.1
unnamed: U3.8, U6.8, U6.9
unnamed: U6.1, U6.5, U6.6
unnamed: U5.4, U7.15 (Q1)
unnamed: BT1.pos, U8.3 (VBAT)
unnamed: U8.1 (X1), Y1.2
unnamed: U8.2 (X2), Y1.1
unnamed: U2.3, U10.3 (Q)
unnamed: C3.1, R5.2, U10.2 (TR), U10.6 (THR)
unnamed: U14.12 (RXDA), U15.12 (R1OUT)
unnamed: U14.15 (TXDA), U15.11 (T1IN)
unnamed: U14.18 (~CTSA), U15.9 (R2OUT)
unnamed: U14.16 (~DTRA), U15.10 (T2IN)
unnamed: C1.1, U15.1 (C1+)
unnamed: C1.2, U15.3 (C1-)
unnamed: C2.1, U15.4 (C2+)
unnamed: C2.2, U15.5 (C2-)
unnamed: J4.3, U15.13 (R1IN)
unnamed: J4.7, U15.8 (R2IN)
unnamed: J4.2, U15.14 (T1OUT)
unnamed: J4.8, U15.7 (T2OUT)
unnamed: C4.1, U15.2 (VS+)
unnamed: C5.2, U15.6 (VS-)
unnamed: U16.9 (S0), U17.4 (D1)
unnamed: U16.7 (S1), U17.7 (D2)
unnamed: U16.6 (S2), U17.8 (D3)

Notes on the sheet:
RESET

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
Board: 2 copper layers, 59 parts (0 on the bottom side), 121 nets, no tracks yet.
